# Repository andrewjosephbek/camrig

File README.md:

# Motorized Camera Tracking Rig

This project implements a compact Camera Motion Platform; integrating custom electronics, embedded firmware, and low-backlash mechanical design. Version 2 is currently in progress (UI firmware is finished, PCB Layout is finished, housing IP)! V1 KiCAD files are for an old version, may be incomplete. 

---

## Version 1: Demo
[Overview Video](https://youtu.be/gTk2HjM0wyA) (1:53)

---

## Version 2: PCB

### 3D:

### Layer 1 (Signal):

### Layer 2 (Ground):

### Layer 3 (Power):

### Layer 4 (Signal):

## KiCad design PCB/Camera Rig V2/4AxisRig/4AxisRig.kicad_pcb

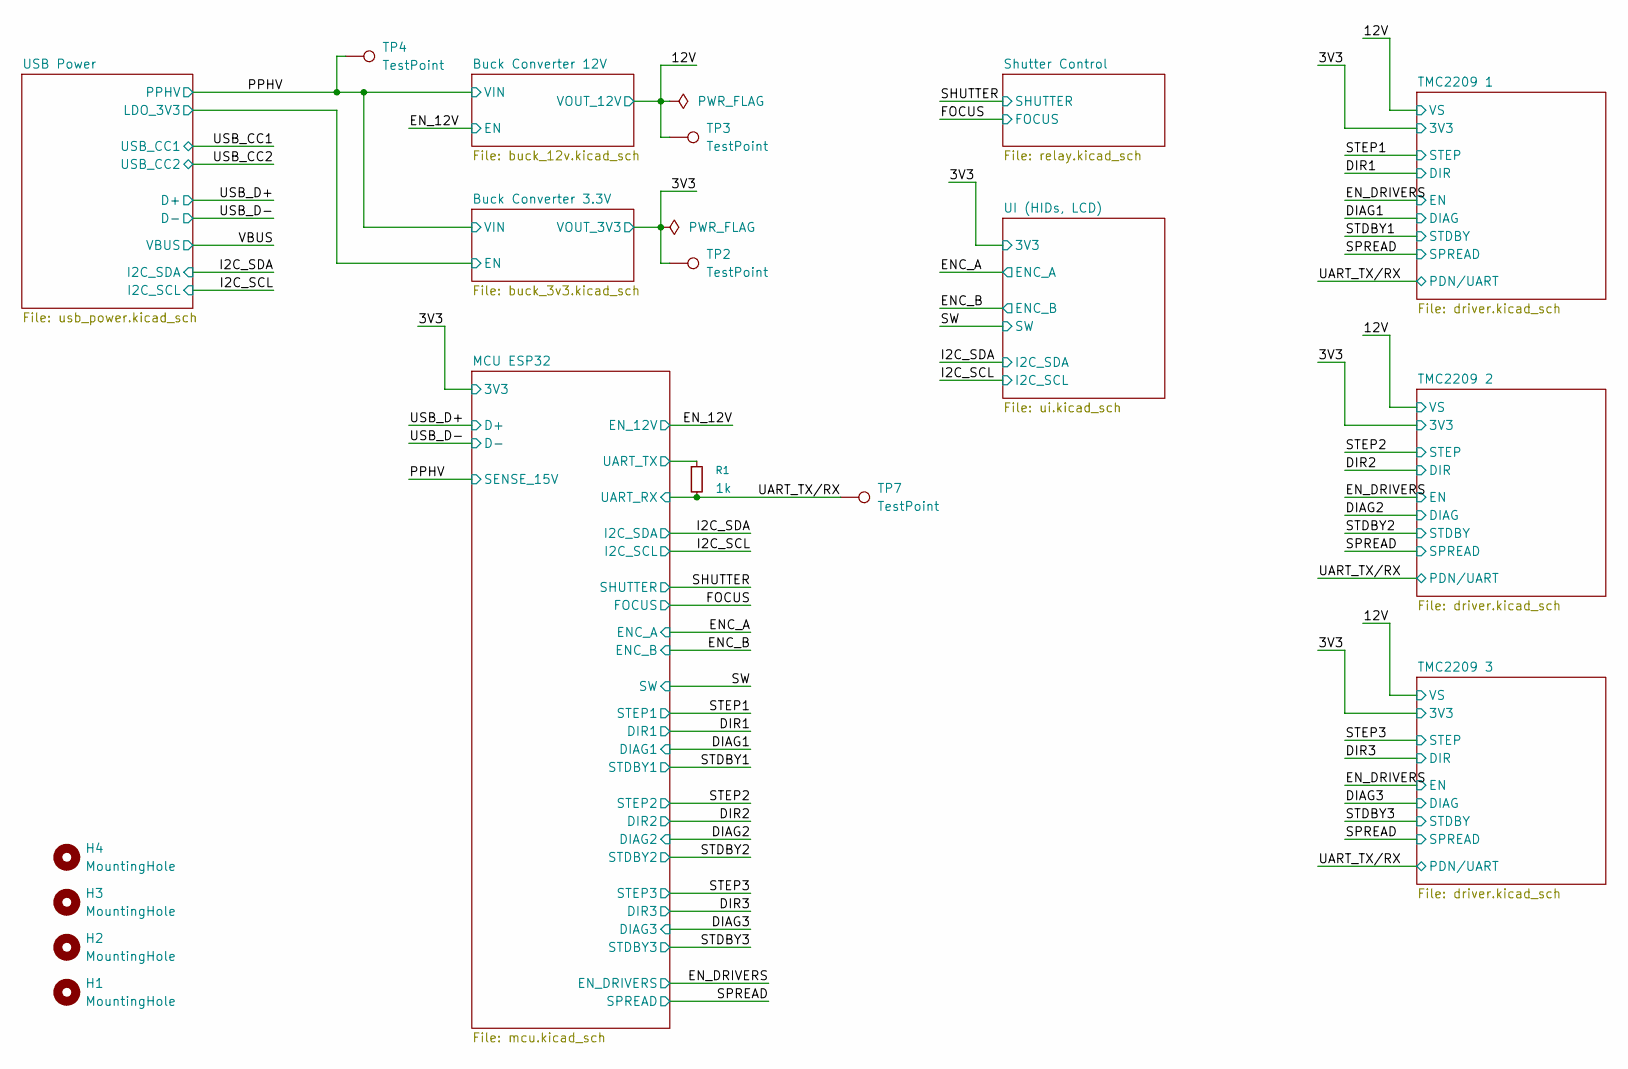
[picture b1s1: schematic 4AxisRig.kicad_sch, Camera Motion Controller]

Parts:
H1, H2, H3, H4: MountingHole; MountingHole_3.2mm_M3
R1: 1k; R_0603_1608Metric_Pad0.98x0.95mm_HandSolder
TP2, TP3, TP4: TestPoint; TestPoint_Pad_1.0x1.0mm
TP7: TestPoint; TestPoint_Keystone_5000-5004_Miniature

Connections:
/3V3: TP2.1; also elsewhere on the board
/12V: TP3.1; also elsewhere on the board
/MCU ESP32/UART_TX: R1.1; also elsewhere on the board
/PPHV: TP4.1; also elsewhere on the board
/UART_TX/RX: R1.2, TP7.1; also elsewhere on the board

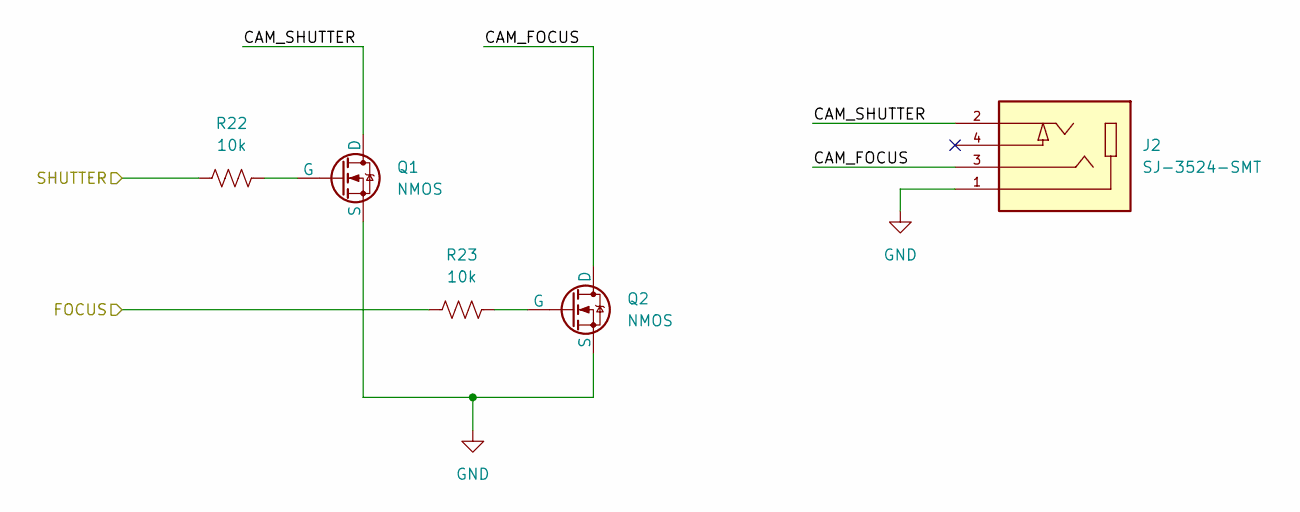
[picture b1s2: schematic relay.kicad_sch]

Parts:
J2: SJ-3524-SMT; CUI_SJ-3524-SMT; PARTREV 1.03; DigiKey_Part_Number CP-3524SJCT-ND
Q1, Q2: NMOS; SOT95P240X111-3N; Part Number 2N7002K
R22, R23: 10k; R_0603_1608Metric_Pad0.98x0.95mm_HandSolder

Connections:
/FOCUS: R23.1; also elsewhere on the board
/SHUTTER: R22.1; also elsewhere on the board
/Shutter Control/CAM_FOCUS: J2.3, Q2.1 (D)
/Shutter Control/CAM_SHUTTER: J2.2, Q1.1 (D)
GND: J2.1, Q1.3 (S), Q2.3 (S); also elsewhere on the board
unnamed: Q1.2 (G), R22.2
unnamed: Q2.2 (G), R23.2

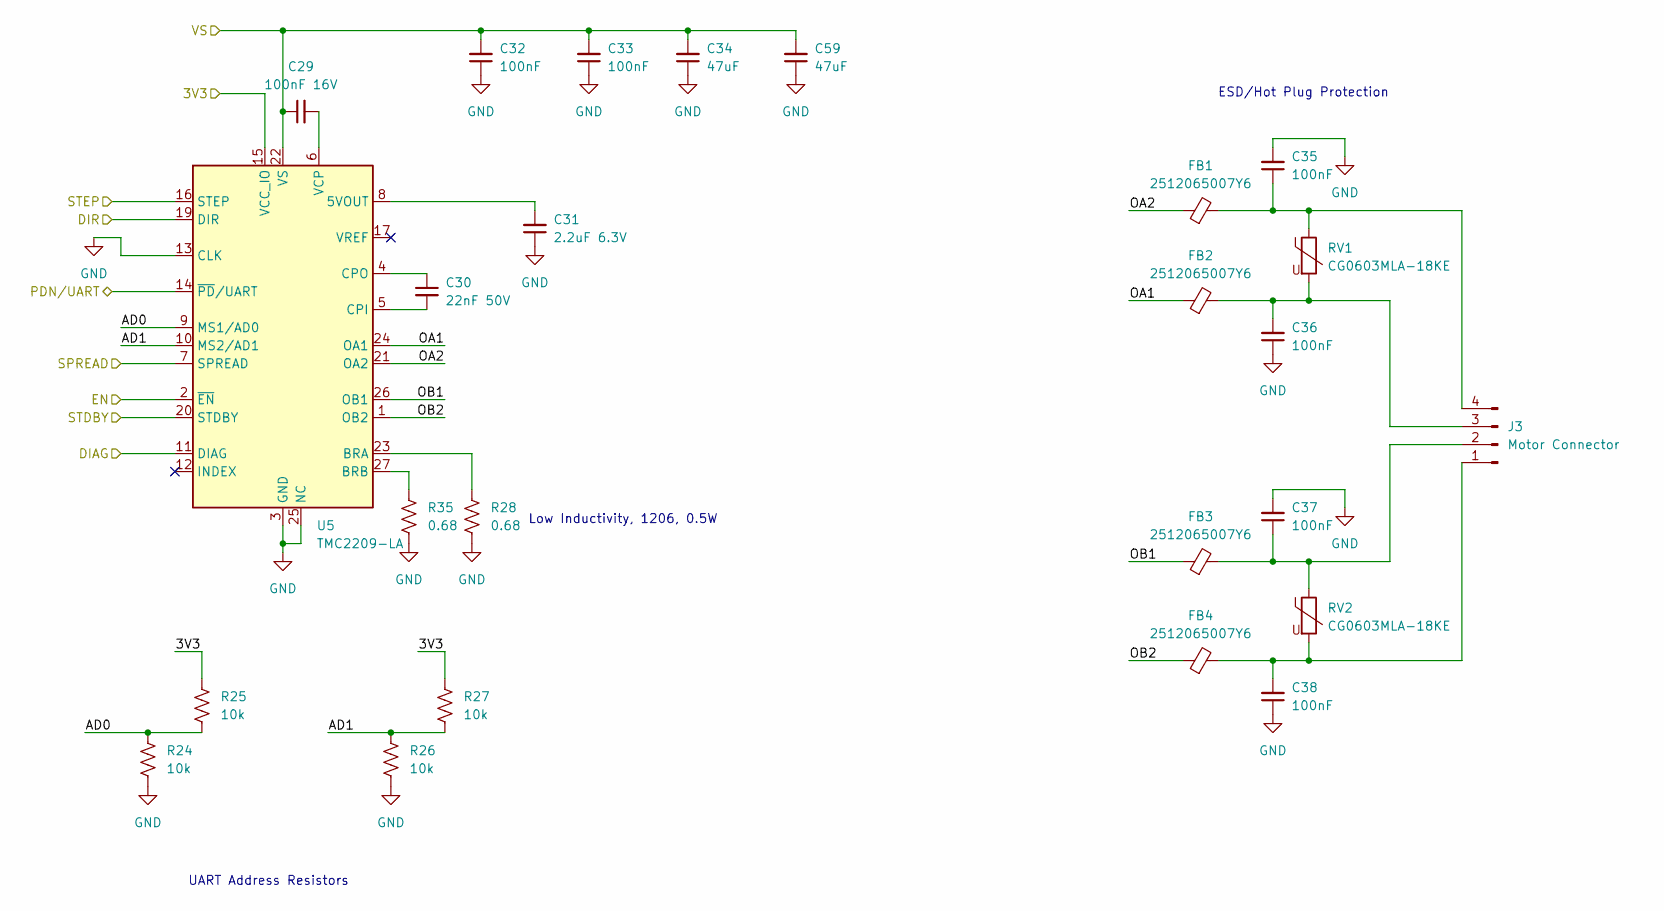
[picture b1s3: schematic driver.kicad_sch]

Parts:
C29: 100nF 16V; C_0603_1608Metric_Pad1.08x0.95mm_HandSolder
C30: 22nF 50V; C_0603_1608Metric_Pad1.08x0.95mm_HandSolder
C31: 2.2uF 6.3V; C_0603_1608Metric_Pad1.08x0.95mm_HandSolder
C32, C33, C35, C36, C37, C38: 100nF; C_0603_1608Metric_Pad1.08x0.95mm_HandSolder
C34, C59: 47uF; C_1210_3225Metric_Pad1.33x2.70mm_HandSolder
FB1, FB2, FB3, FB4: 2512065007Y6; L_1206_3216Metric_Pad1.22x1.90mm_HandSolder
J3: Motor Connector; PinHeader_1x04_P2.54mm_Horizontal
R24, R25, R26, R27: 10k; R_0603_1608Metric_Pad0.98x0.95mm_HandSolder
R28, R35: 0.68; R_1206_3216Metric_Pad1.30x1.75mm_HandSolder
RV1, RV2: CG0603MLA-18KE; R_1206_3216Metric_Pad1.30x1.75mm_HandSolder
U5: TMC2209-LA; VQFN-28-1EP_5x5mm_P0.5mm_EP3.7x3.7mm_ThermalVias; Part Number TMC2209-LA

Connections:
/3V3: R25.2, R27.2, U5.15 (VCC_IO); also elsewhere on the board
/12V: C29.1, C32.2, C33.2, C34.2, C59.2, U5.22 (VS), U5.28 (VS); also elsewhere on the board
/DIAG1: U5.11 (DIAG); also elsewhere on the board
/DIR1: U5.19 (DIR); also elsewhere on the board
/EN_DRIVERS: U5.2 (~EN); also elsewhere on the board
/SPREAD: U5.7 (SPREAD); also elsewhere on the board
/STDBY1: U5.20 (STDBY); also elsewhere on the board
/STEP1: U5.16 (STEP); also elsewhere on the board
/TMC2209 1/AD0: R24.2, R25.1, U5.9 (MS1/AD0)
/TMC2209 1/AD1: R26.2, R27.1, U5.10 (MS2/AD1)
/TMC2209 1/OA1: FB2.1, U5.24 (OA1)
/TMC2209 1/OA2: FB1.1, U5.21 (OA2)
/TMC2209 1/OB1: FB3.1, U5.26 (OB1)
/TMC2209 1/OB2: FB4.1, U5.1 (OB2)
/UART_TX/RX: U5.14 (~PD/UART); also elsewhere on the board
GND: C31.1, C32.1, C33.1, C34.1, C35.2, C36.1, C37.2, C38.1, C59.1, R24.1, R26.1, R28.1, R35.1, U5.3 (GND), U5.13 (CLK), U5.18 (GND), U5.25 (NC), U5.29 (GND); also elsewhere on the board
unnamed: C38.2, FB4.2, J3.1, RV2.2
unnamed: C37.1, FB3.2, J3.2, RV2.1
unnamed: C36.2, FB2.2, J3.3, RV1.2
unnamed: C35.1, FB1.2, J3.4, RV1.1
unnamed: C31.2, U5.8 (5VOUT)
unnamed: R28.2, U5.23 (BRA)
unnamed: R35.2, U5.27 (BRB)
unnamed: C30.2, U5.5 (CPI)
unnamed: C30.1, U5.4 (CPO)
unnamed: C29.2, U5.6 (VCP)

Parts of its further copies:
C39, C49: 100nF 16V; C_0603_1608Metric_Pad1.08x0.95mm_HandSolder
C40, C50: 22nF 50V; C_0603_1608Metric_Pad1.08x0.95mm_HandSolder
C41, C51: 2.2uF 6.3V; C_0603_1608Metric_Pad1.08x0.95mm_HandSolder
C42, C43, C45, C46, C47, C48, C52, C53, C55, C56, C57, C58: 100nF; C_0603_1608Metric_Pad1.08x0.95mm_HandSolder
C44, C54, C60, C61: 47uF; C_1210_3225Metric_Pad1.33x2.70mm_HandSolder
FB5, FB6, FB7, FB8, FB9, FB10, FB11, FB12: 2512065007Y6; L_1206_3216Metric_Pad1.22x1.90mm_HandSolder
J4, J6: Motor Connector; PinHeader_1x04_P2.54mm_Horizontal
R29, R34, R42, R43: 0.68; R_1206_3216Metric_Pad1.30x1.75mm_HandSolder
R30, R31, R32, R33, R38, R39, R40, R41: 10k; R_0603_1608Metric_Pad0.98x0.95mm_HandSolder
RV3, RV4, RV5, RV6: CG0603MLA-18KE; R_1206_3216Metric_Pad1.30x1.75mm_HandSolder
U6, U7: TMC2209-LA; VQFN-28-1EP_5x5mm_P0.5mm_EP3.7x3.7mm_ThermalVias; Part Number TMC2209-LA

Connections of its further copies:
/3V3: R31.2, R33.2, R39.2, R41.2, U6.15 (VCC_IO), U7.15 (VCC_IO); also elsewhere on the board
/12V: C39.1, C42.2, C43.2, C44.2, C49.1, C52.2, C53.2, C54.2, C60.2, C61.2, U6.22 (VS), U6.28 (VS), U7.22 (VS), U7.28 (VS); also elsewhere on the board
/DIAG2: U6.11 (DIAG); also elsewhere on the board
/DIAG3: U7.11 (DIAG); also elsewhere on the board
/DIR2: U6.19 (DIR); also elsewhere on the board
/DIR3: U7.19 (DIR); also elsewhere on the board
/EN_DRIVERS: U6.2 (~EN), U7.2 (~EN); also elsewhere on the board
/SPREAD: U6.7 (SPREAD), U7.7 (SPREAD); also elsewhere on the board
/STDBY2: U6.20 (STDBY); also elsewhere on the board
/STDBY3: U7.20 (STDBY); also elsewhere on the board
/STEP2: U6.16 (STEP); also elsewhere on the board
/STEP3: U7.16 (STEP); also elsewhere on the board
/TMC2209 2/AD0: R30.2, R31.1, U6.9 (MS1/AD0)
/TMC2209 2/AD1: R32.2, R33.1, U6.10 (MS2/AD1)
/TMC2209 2/OA1: FB6.1, U6.24 (OA1)
/TMC2209 2/OA2: FB5.1, U6.21 (OA2)
/TMC2209 2/OB1: FB7.1, U6.26 (OB1)
/TMC2209 2/OB2: FB8.1, U6.1 (OB2)
/TMC2209 3/AD0: R38.2, R39.1, U7.9 (MS1/AD0)
/TMC2209 3/AD1: R40.2, R41.1, U7.10 (MS2/AD1)
/TMC2209 3/OA1: FB10.1, U7.24 (OA1)
/TMC2209 3/OA2: FB9.1, U7.21 (OA2)
/TMC2209 3/OB1: FB11.1, U7.26 (OB1)
/TMC2209 3/OB2: FB12.1, U7.1 (OB2)
/UART_TX/RX: U6.14 (~PD/UART), U7.14 (~PD/UART); also elsewhere on the board
GND: C41.1, C42.1, C43.1, C44.1, C45.2, C46.1, C47.2, C48.1, C51.1, C52.1, C53.1, C54.1, C55.2, C56.1, C57.2, C58.1, C60.1, C61.1, R29.1, R30.1, R32.1, R34.1, R38.1, R40.1, R42.1, R43.1, U6.3 (GND), U6.13 (CLK), U6.18 (GND), U6.25 (NC), U6.29 (GND), U7.3 (GND), U7.13 (CLK), U7.18 (GND), U7.25 (NC), U7.29 (GND); also elsewhere on the board
unnamed: C48.2, FB8.2, J4.1, RV4.2
unnamed: C47.1, FB7.2, J4.2, RV4.1
unnamed: C46.2, FB6.2, J4.3, RV3.2
unnamed: C45.1, FB5.2, J4.4, RV3.1
unnamed: C58.2, FB12.2, J6.1, RV6.2
unnamed: C57.1, FB11.2, J6.2, RV6.1
unnamed: C56.2, FB10.2, J6.3, RV5.2
unnamed: C55.1, FB9.2, J6.4, RV5.1
unnamed: C41.2, U6.8 (5VOUT)
unnamed: R29.2, U6.23 (BRA)
unnamed: R42.2, U6.27 (BRB)
unnamed: C40.2, U6.5 (CPI)
unnamed: C40.1, U6.4 (CPO)
unnamed: C39.2, U6.6 (VCP)
unnamed: C51.2, U7.8 (5VOUT)
unnamed: R34.2, U7.23 (BRA)
unnamed: R43.2, U7.27 (BRB)
unnamed: C50.2, U7.5 (CPI)
unnamed: C50.1, U7.4 (CPO)
unnamed: C49.2, U7.6 (VCP)

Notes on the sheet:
UART Address Resistors
ESD/Hot Plug Protection
Low Inductivity, 1206, 0.5W

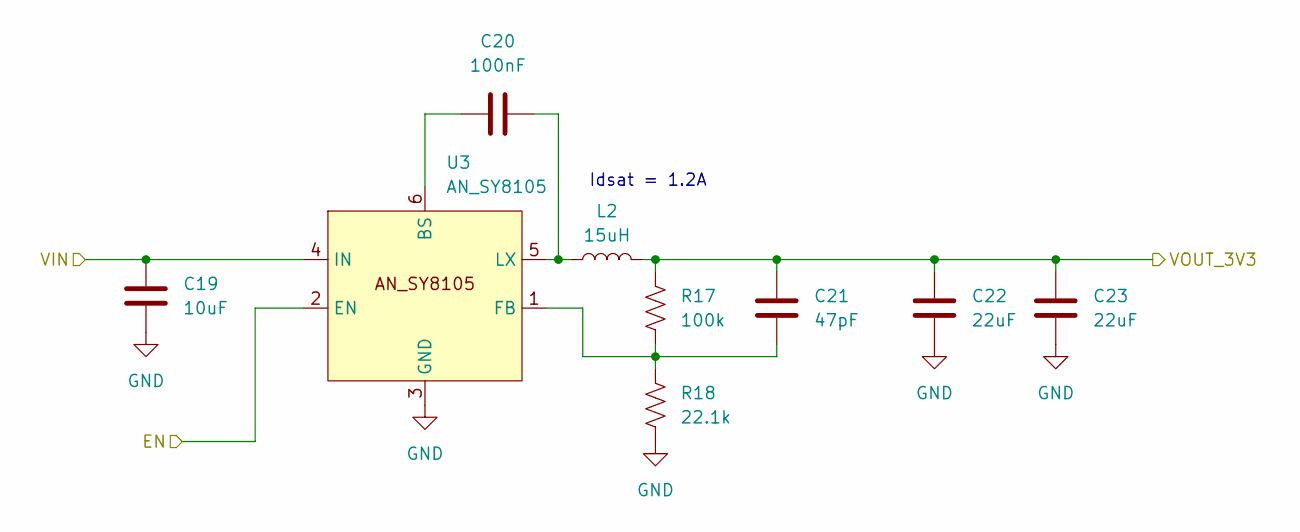
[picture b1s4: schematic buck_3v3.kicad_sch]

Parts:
C19: 10uF; C_0603_1608Metric_Pad1.08x0.95mm_HandSolder
C20: 100nF; C_0603_1608Metric_Pad1.08x0.95mm_HandSolder
C21: 47pF; C_0603_1608Metric_Pad1.08x0.95mm_HandSolder
C22, C23: 22uF; C_1206_3216Metric_Pad1.33x1.80mm_HandSolder
L2: 15uH; DR74; Part Number DR74-150-R
R17: 100k; R_0603_1608Metric_Pad0.98x0.95mm_HandSolder
R18: 22.1k; R_0603_1608Metric_Pad0.98x0.95mm_HandSolder
U3: AN_SY8105; TSOT-23-6_HandSoldering; Part Number AN_SY8105

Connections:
/3V3: C21.1, C22.1, C23.1, L2.2, R17.1; also elsewhere on the board
/PPHV: C19.1, U3.4 (IN); also elsewhere on the board
/USB Power/LDO_3V3: U3.2 (EN); also elsewhere on the board
GND: C19.2, C22.2, C23.2, R18.2, U3.3 (GND); also elsewhere on the board
unnamed: C20.2, U3.6 (BS)
unnamed: C21.2, R17.2, R18.1, U3.1 (FB)
unnamed: C20.1, L2.1, U3.5 (LX)

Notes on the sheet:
Idsat = 1.2A

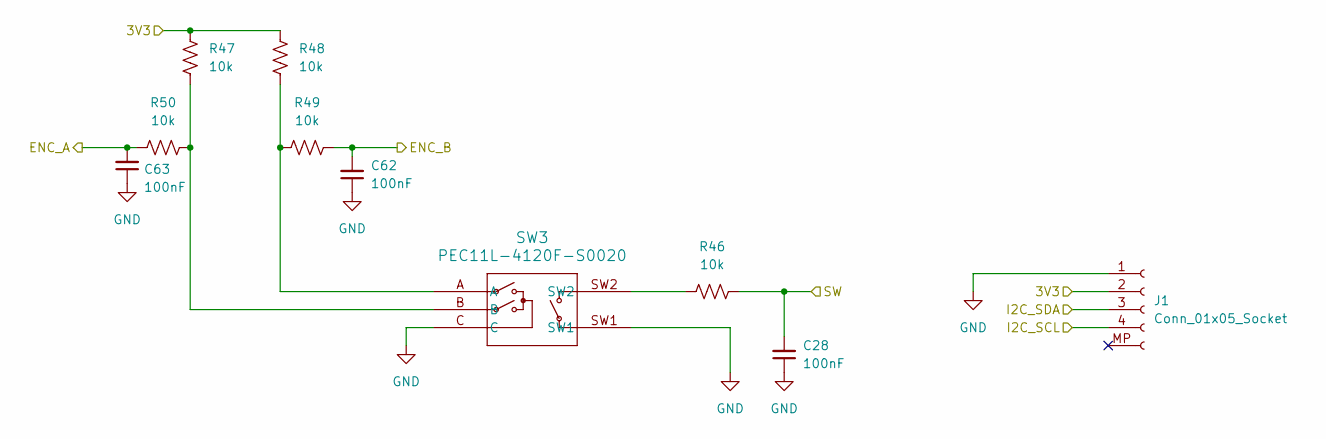
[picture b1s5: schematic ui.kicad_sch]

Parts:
C28, C62, C63: 100nF; C_0603_1608Metric_Pad1.08x0.95mm_HandSolder
J1: Conn_01x05_Socket; JST_SH_BM04B-SRSS-TB_1x04-1MP_P1.00mm_Vertical
R46, R47, R48, R49, R50: 10k; R_0603_1608Metric_Pad0.98x0.95mm_HandSolder
SW3: PEC11L-4120F-S0020; PEC11L-4x20F-Sxxx_BRN

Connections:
/3V3: J1.2, R47.1, R48.1; also elsewhere on the board
/ENC_A: C63.2, R50.1; also elsewhere on the board
/ENC_B: C62.2, R49.2; also elsewhere on the board
/I2C_SCL: J1.4; also elsewhere on the board
/I2C_SDA: J1.3; also elsewhere on the board
/SW: C28.2, R46.1; also elsewhere on the board
GND: C28.1, C62.1, C63.1, J1.1, SW3.C, SW3.SW1; also elsewhere on the board
unnamed: R46.2, SW3.SW2
unnamed: R47.2, R50.2, SW3.B
unnamed: R48.2, R49.1, SW3.A

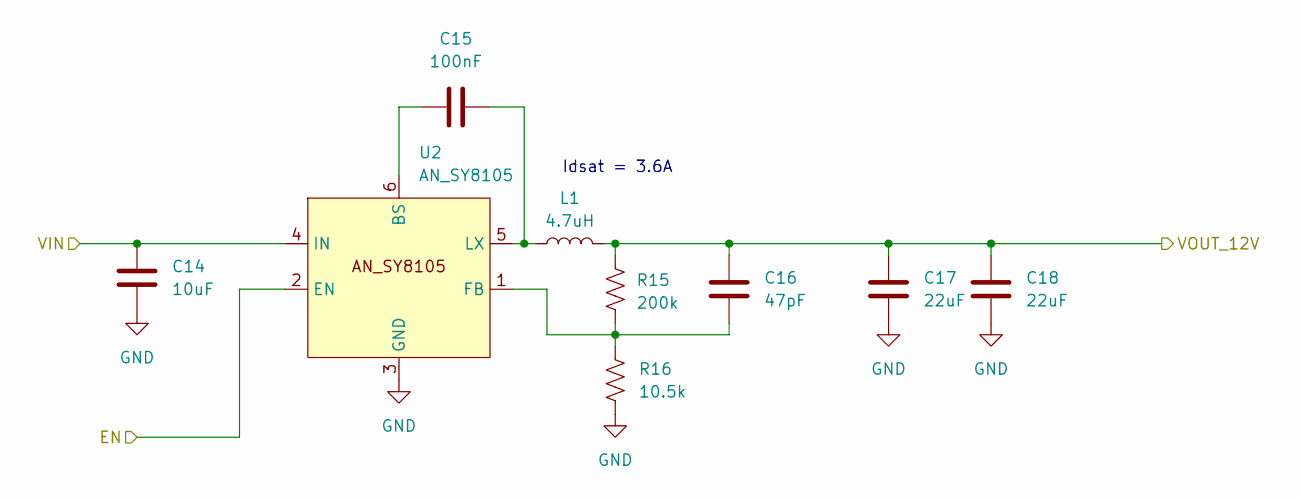
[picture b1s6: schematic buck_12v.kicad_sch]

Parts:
C14: 10uF; C_0603_1608Metric_Pad1.08x0.95mm_HandSolder
C15: 100nF; C_0603_1608Metric_Pad1.08x0.95mm_HandSolder
C16: 47pF; C_0603_1608Metric_Pad1.08x0.95mm_HandSolder
C17, C18: 22uF; C_1206_3216Metric_Pad1.33x1.80mm_HandSolder
L1: 4.7uH; DR74; Part Number DR74-4R7-R
R15: 200k; R_0603_1608Metric_Pad0.98x0.95mm_HandSolder
R16: 10.5k; R_0603_1608Metric_Pad0.98x0.95mm_HandSolder
U2: AN_SY8105; TSOT-23-6_HandSoldering; Part Number AN_SY8105

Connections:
/12V: C16.1, C17.1, C18.1, L1.2, R15.1; also elsewhere on the board
/EN_12V: U2.2 (EN); also elsewhere on the board
/PPHV: C14.1, U2.4 (IN); also elsewhere on the board
GND: C14.2, C17.2, C18.2, R16.2, U2.3 (GND); also elsewhere on the board
unnamed: C15.2, U2.6 (BS)
unnamed: C16.2, R15.2, R16.1, U2.1 (FB)
unnamed: C15.1, L1.1, U2.5 (LX)

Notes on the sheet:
Idsat = 3.6A

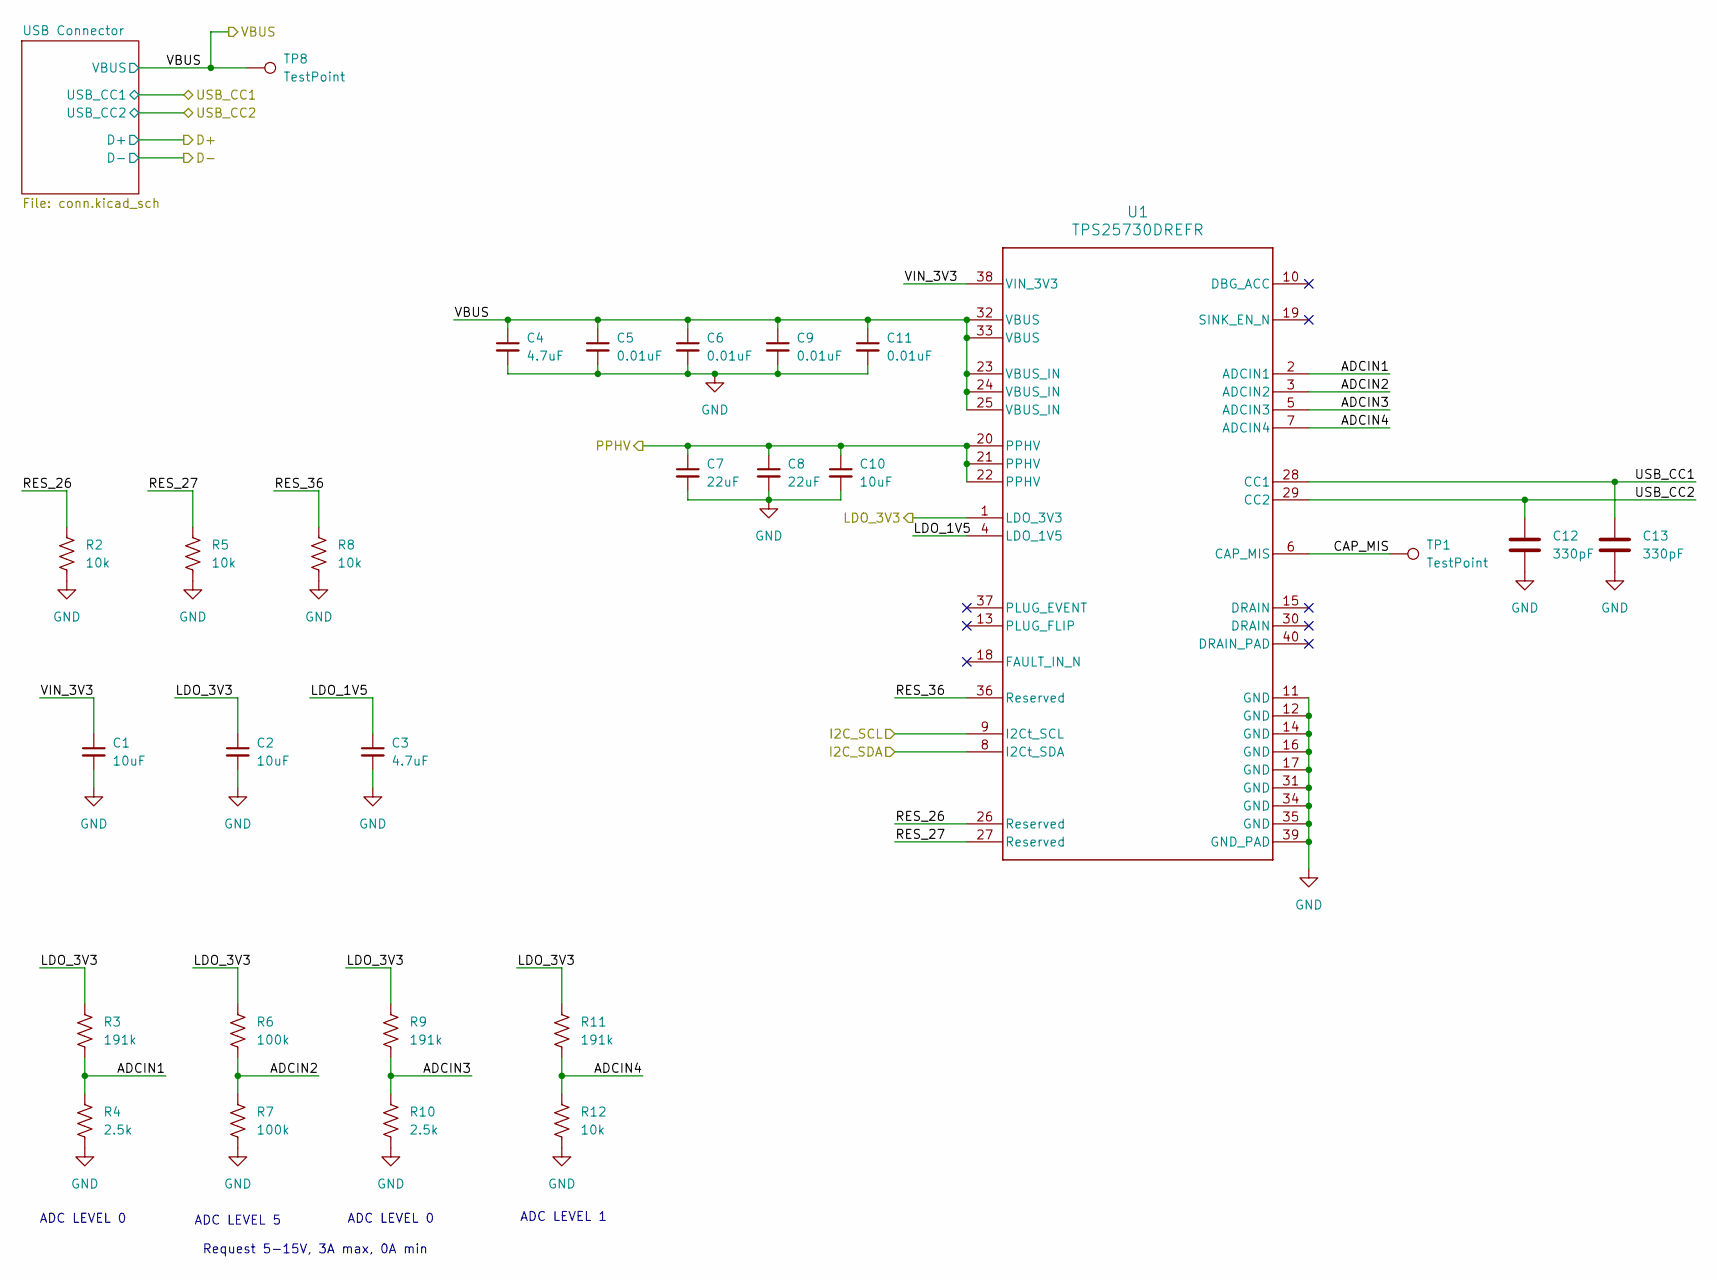
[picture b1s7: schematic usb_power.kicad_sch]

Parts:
C1, C2, C10: 10uF; C_0603_1608Metric_Pad1.08x0.95mm_HandSolder
C3, C4: 4.7uF; C_0603_1608Metric_Pad1.08x0.95mm_HandSolder
C5, C6, C9, C11: 0.01uF; C_0603_1608Metric_Pad1.08x0.95mm_HandSolder
C7, C8: 22uF; C_1206_3216Metric_Pad1.33x1.80mm_HandSolder
C12, C13: 330pF; C_0603_1608Metric_Pad1.08x0.95mm_HandSolder
R2, R5, R8, R12: 10k; R_0603_1608Metric_Pad0.98x0.95mm_HandSolder
R3, R9, R11: 191k; R_0603_1608Metric_Pad0.98x0.95mm_HandSolder
R4, R10: 2.5k; R_0603_1608Metric_Pad0.98x0.95mm_HandSolder
R6, R7: 100k; R_0603_1608Metric_Pad0.98x0.95mm_HandSolder
TP1, TP8: TestPoint; TestPoint_Pad_1.0x1.0mm
U1: TPS25730DREFR; REF0038A-MFG; Part Number TPS25730DREFR

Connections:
/I2C_SCL: U1.9 (I2Ct_SCL); also elsewhere on the board
/I2C_SDA: U1.8 (I2Ct_SDA); also elsewhere on the board
/PPHV: C7.1, C8.1, C10.1, U1.20 (PPHV), U1.21 (PPHV), U1.22 (PPHV); also elsewhere on the board
/USB Power/ADCIN1: R3.2, R4.1, U1.2 (ADCIN1)
/USB Power/ADCIN2: R6.2, R7.1, U1.3 (ADCIN2)
/USB Power/ADCIN3: R9.2, R10.1, U1.5 (ADCIN3)
/USB Power/ADCIN4: R11.2, R12.1, U1.7 (ADCIN4)
/USB Power/CAP_MIS: TP1.1, U1.6 (CAP_MIS)
/USB Power/LDO_1V5: C3.1, U1.4 (LDO_1V5)
/USB Power/LDO_3V3: C2.1, R3.1, R6.1, R9.1, R11.1, U1.1 (LDO_3V3); also elsewhere on the board
/USB Power/RES_26: R2.1, U1.26 (Reserved)
/USB Power/RES_27: R5.1, U1.27 (Reserved)
/USB Power/RES_36: R8.1, U1.36 (Reserved)
/USB Power/VIN_3V3: C1.1, U1.38 (VIN_3V3)
/USB_CC1: C13.1, U1.28 (CC1); also elsewhere on the board
/USB_CC2: C12.1, U1.29 (CC2); also elsewhere on the board
/VBUS: C4.1, C5.1, C6.1, C9.1, C11.1, TP8.1, U1.23 (VBUS_IN), U1.24 (VBUS_IN), U1.25 (VBUS_IN), U1.32 (VBUS), U1.33 (VBUS); also elsewhere on the board
GND: C1.2, C2.2, C3.2, C4.2, C5.2, C6.2, C7.2, C8.2, C9.2, C10.2, C11.2, C12.2, C13.2, R2.2, R4.2, R5.2, R7.2, R8.2, R10.2, R12.2, U1.11 (GND), U1.12 (GND), U1.14 (GND), U1.16 (GND), U1.17 (GND), U1.31 (GND), U1.34 (GND), U1.35 (GND), U1.39 (GND_PAD); also elsewhere on the board

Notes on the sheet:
Request 5-15V, 3A max, 0A min
ADC LEVEL 5
ADC LEVEL 0
ADC LEVEL 0
ADC LEVEL 1

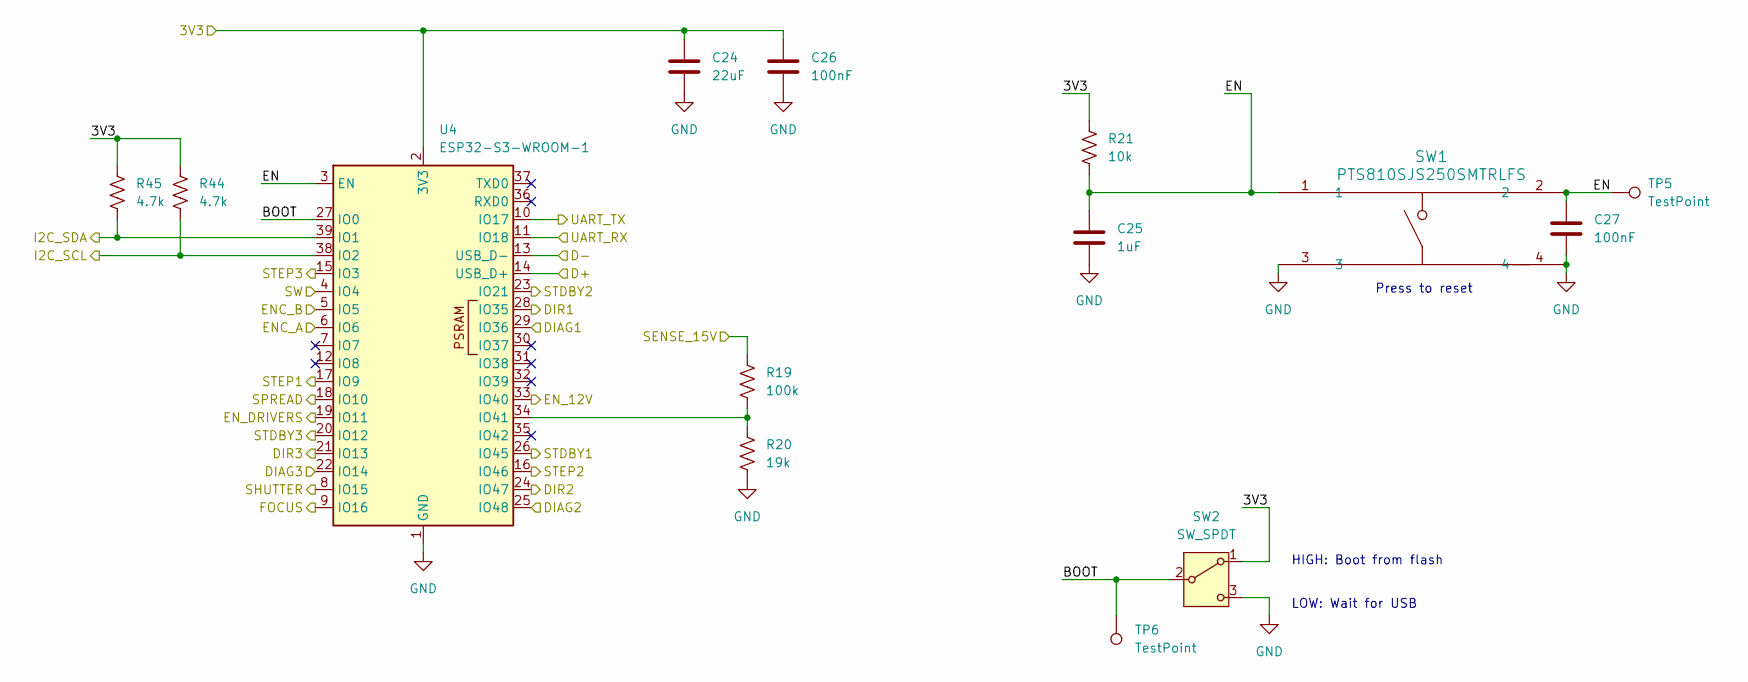
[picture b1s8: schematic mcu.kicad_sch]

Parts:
C24: 22uF; C_1206_3216Metric_Pad1.33x1.80mm_HandSolder
C25: 1uF; C_0603_1608Metric_Pad1.08x0.95mm_HandSolder
C26, C27: 100nF; C_0603_1608Metric_Pad1.08x0.95mm_HandSolder
R19: 100k; R_0603_1608Metric_Pad0.98x0.95mm_HandSolder
R20: 19k; R_0603_1608Metric_Pad0.98x0.95mm_HandSolder
R21: 10k; R_0603_1608Metric_Pad0.98x0.95mm_HandSolder
R44, R45: 4.7k; R_0603_1608Metric_Pad0.98x0.95mm_HandSolder
SW1: PTS810SJS250SMTRLFS; SMT_MTRLFS_CNK
SW2: SW_SPDT; SS12D07_CNK
TP5, TP6: TestPoint; TestPoint_Pad_1.0x1.0mm
U4: ESP32-S3-WROOM-1; Part Number ESP32-S3-WROOM-1

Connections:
/3V3: C24.1, C26.1, R21.2, R44.2, R45.2, SW2.1 (A), U4.2 (3V3); also elsewhere on the board
/DIAG1: U4.29 (IO36); also elsewhere on the board
/DIAG2: U4.25 (IO48); also elsewhere on the board
/DIAG3: U4.22 (IO14); also elsewhere on the board
/DIR1: U4.28 (IO35); also elsewhere on the board
/DIR2: U4.24 (IO47); also elsewhere on the board
/DIR3: U4.21 (IO13); also elsewhere on the board
/ENC_A: U4.6 (IO6); also elsewhere on the board
/ENC_B: U4.5 (IO5); also elsewhere on the board
/EN_12V: U4.33 (IO40); also elsewhere on the board
/EN_DRIVERS: U4.19 (IO11); also elsewhere on the board
/FOCUS: U4.9 (IO16); also elsewhere on the board
/I2C_SCL: R44.1, U4.38 (IO2); also elsewhere on the board
/I2C_SDA: R45.1, U4.39 (IO1); also elsewhere on the board
/MCU ESP32/BOOT: SW2.2 (B), TP6.1, U4.27 (IO0)
/MCU ESP32/EN: C25.2, C27.1, R21.1, SW1.1, SW1.2, TP5.1, U4.3 (EN)
/MCU ESP32/UART_TX: U4.10 (IO17); also elsewhere on the board
/PPHV: R19.2; also elsewhere on the board
/SHUTTER: U4.8 (IO15); also elsewhere on the board
/SPREAD: U4.18 (IO10); also elsewhere on the board
/STDBY1: U4.26 (IO45); also elsewhere on the board
/STDBY2: U4.23 (IO21); also elsewhere on the board
/STDBY3: U4.20 (IO12); also elsewhere on the board
/STEP1: U4.17 (IO9); also elsewhere on the board
/STEP2: U4.16 (IO46); also elsewhere on the board
/STEP3: U4.15 (IO3); also elsewhere on the board
/SW: U4.4 (IO4); also elsewhere on the board
/UART_TX/RX: U4.11 (IO18); also elsewhere on the board
/USB_D+: U4.14 (USB_D+); also elsewhere on the board
/USB_D-: U4.13 (USB_D-); also elsewhere on the board
GND: C24.2, C25.1, C26.2, C27.2, R20.1, SW1.3, SW1.4, SW2.3 (C), U4.1 (GND), U4.40 (GND), U4.41 (GND); also elsewhere on the board
unnamed: R19.1, R20.2, U4.34 (IO41)

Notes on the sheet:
Press to reset
HIGH: Boot from flash LOW: Wait for USB

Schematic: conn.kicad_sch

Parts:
D1, D2, D3, D4: ESD441; D_0402_1005Metric_Pad0.77x0.64mm_HandSolder
D5: T4F10A; Nexperia_CFP3_SOD-123W
J5: USB_C_Receptacle_USB2.0_16P; CONN_8p94X6p5X3p16_12L_GCC
R36, R37: 5.1k+-10%; R_0603_1608Metric_Pad0.98x0.95mm_HandSolder

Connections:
/USB_CC1: D3.1 (K), J5.A5 (CC1), R36.1; also elsewhere on the board
/USB_CC2: D4.1 (K), J5.B5 (CC2), R37.1; also elsewhere on the board
/USB_D+: D1.1 (K), J5.A6 (D+), J5.B6 (D+); also elsewhere on the board
/USB_D-: D2.1 (K), J5.A7 (D-), J5.B7 (D-); also elsewhere on the board
/VBUS: D5.1 (K), J5.A4 (VBUS), J5.A9 (VBUS), J5.B4 (VBUS), J5.B9 (VBUS); also elsewhere on the board
GND: D1.2 (A), D2.2 (A), D3.2 (A), D4.2 (A), D5.2 (A), J5.A1 (GND), J5.A12 (GND), J5.B1 (GND), J5.B12 (GND), J5.S1 (SHIELD), R36.2, R37.2; also elsewhere on the board

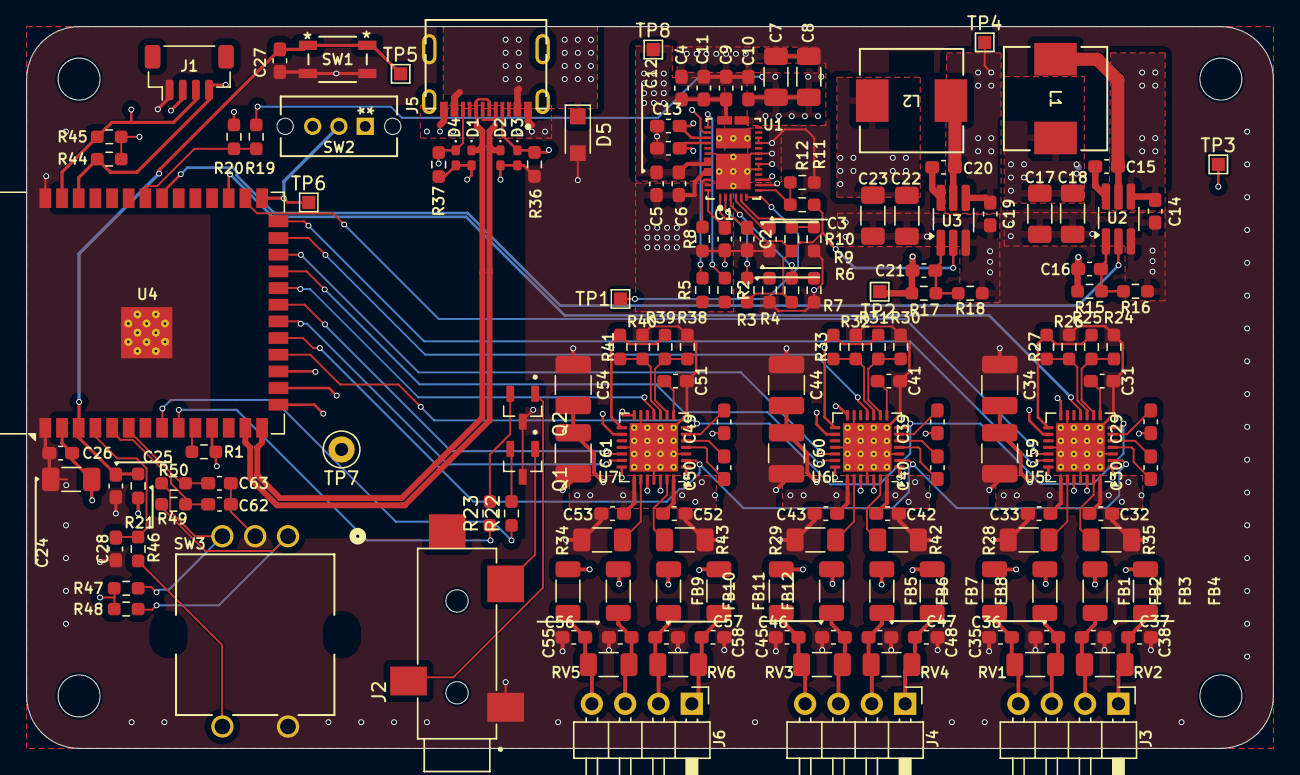
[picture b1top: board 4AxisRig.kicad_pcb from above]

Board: 4 copper layers, 95.0 x 55.0 mm, 166 parts (0 on the bottom side), 108 nets.

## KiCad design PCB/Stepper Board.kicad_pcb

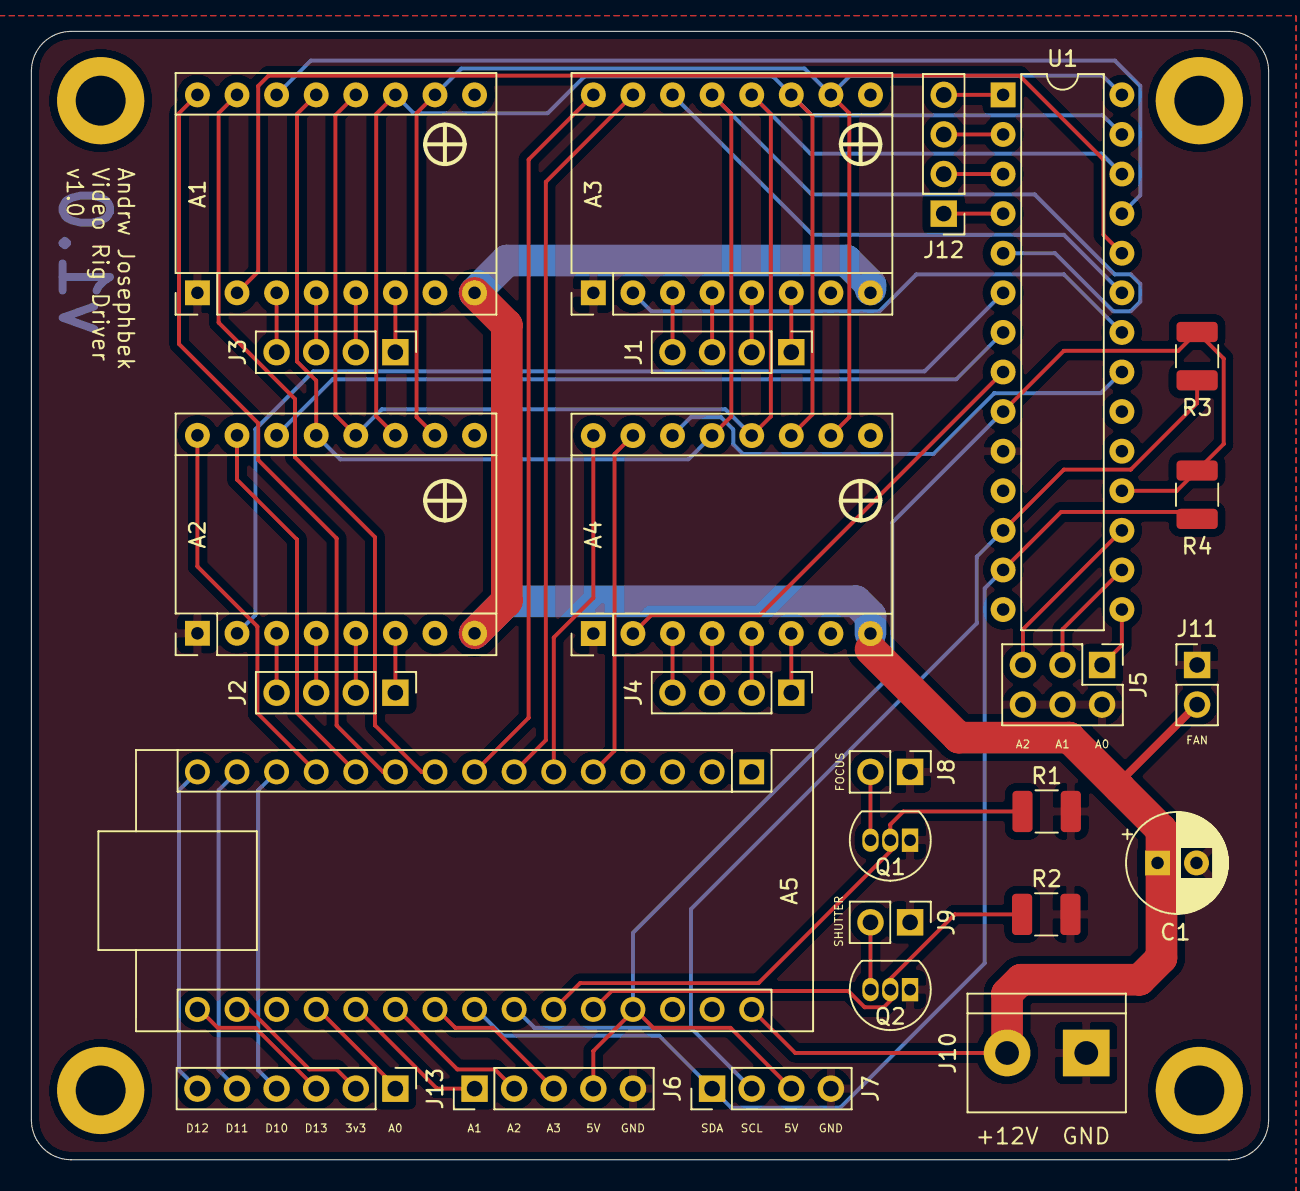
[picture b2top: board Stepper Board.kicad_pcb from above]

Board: 2 copper layers, 79.4 x 72.4 mm, 30 parts (0 on the bottom side), 61 nets.

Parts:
 : MountingHole_3.2mm_M3_DIN965_Pad
 #2,  #3,  #4: MountingHole_3.2mm_M3_DIN965_Pad
A1, A2, A3, A4: Pololu_Breakout_DRV8825; Pololu_Breakout-16_15.2x20.3mm
A5: Arduino_Nano_v3.x; Arduino_Nano
C1: 220uF; CP_Radial_D6.3mm_P2.50mm
J1, J2, J3, J4: Stepper Header; PinHeader_1x04_P2.54mm_Vertical
J5: Address Header; PinHeader_2x03_P2.54mm_Vertical
J6: R.Encoder Header; PinHeader_1x05_P2.54mm_Vertical
J7: LCD Header; PinHeader_1x04_P2.54mm_Vertical
J8: Focus; PinHeader_1x02_P2.54mm_Vertical
J9: Shot; PinHeader_1x02_P2.54mm_Vertical
J10: Power (+12V); TerminalBlock_bornier-2_P5.08mm
J11: Fan Header; PinHeader_1x02_P2.54mm_Vertical
J12: Extra Header I2C; PinHeader_1x04_P2.54mm_Vertical
J13: Extra Header Direct; PinHeader_1x06_P2.54mm_Vertical
Q1, Q2: 2N7000; TO-92_Inline
R3, R4, R7, R8: SM 10K; R_1210_3225Metric_Pad1.30x2.65mm_HandSolder
U1: MCP23017_SP; DIP-28_W7.62mm

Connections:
+3V3: A5.17, J13.2
+5V: A5.27, J6.4, J7.3, R3.1, R4.1, U1.9, U1.18
A0: A5.19, J13.1
A1: A5.20, J6.1
A1(1): A1.4, J1.3
A1(2): A2.4, J2.3
A1(3): A3.4, J3.3
A1(4): A4.4, J4.3
A2: A5.21, J6.2
A2(1): A1.3, J1.4
A2(2): A2.3, J2.4
A2(3): A3.3, J3.4
A2(4): A4.3, J4.4
A3: A5.22, J6.3
A6: A5.25, Q1.2
A7: A5.26, Q2.2
B1(1): A1.5, J1.2
B1(2): A2.5, J2.2
B1(3): A3.5, J3.2
B1(4): A4.5, J4.2
B2(1): A1.6, J1.1
B2(2): A2.6, J2.1
B2(3): A3.6, J3.1
B2(4): A4.6, J4.1
D13: A5.16, J13.3
DIR1: A1.16, A5.8
DIR2: A2.16, A5.12
DIR3: A3.16, A5.10
DIR4: A4.16, A5.6
FLT1: A1.2, U1.22
FLT2: A2.2, U1.6
FLT3: A3.2, U1.24
FLT4: A4.2, U1.8
GND: A1.1, A2.1, A3.1, A4.1, A5.29, C1.2, J5.2, J5.4, J5.6, J6.5, J7.4, J8.1, J9.1, J10.1, J11.1, Q1.1, Q2.1, R7.1, R8.1, U1.10
M0: A1.10, A2.10, A3.10, A4.10, U1.28
M1: A1.11, A2.11, A3.11, A4.11, U1.27
M2: A1.12, A2.12, A3.12, A4.12, U1.26
unnamed: A5.13, J13.4
unnamed: A5.14, J13.5
unnamed: A5.15, J13.6
unnamed: J5.1, U1.15
unnamed: J5.3, U1.16
unnamed: J5.5, U1.17
unnamed: J8.2, Q1.3
unnamed: J9.2, Q2.3
unnamed: J12.1, U1.4
unnamed: J12.2, U1.3
unnamed: J12.3, U1.2
unnamed: J12.4, U1.1
RST: A1.13, A2.13, A3.13, A4.13, U1.5
SCK: A5.24, J7.2, R4.2, U1.12
SDA: A5.23, J7.1, R3.2, U1.13
SLEEP1: A1.14, U1.23
SLEEP2: A2.14, U1.7
SLEEP3: A3.14, U1.25
SLEEP4: A4.14, U1.21
STEP1: A1.15, A5.7
STEP2: A2.15, A5.11
STEP3: A3.15, A5.9
STEP4: A4.15, A5.5
VCC: A1.8, A2.8, A3.8, A4.8, A5.30, C1.1, J10.2, J11.2

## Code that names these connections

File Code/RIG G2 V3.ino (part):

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#include <Adafruit_MCP23017.h>

//Definitions
#define STEP4 2
#define DIR4 3
#define STEP1 4
#define DIR1 5
#define STEP3 6
#define DIR3 7
#define STEP2 8
#define DIR2 9

#define SDA 4
#define SCL 5
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#define M2 5

#define RESET 12
#define SLEEP1 2
#define SLEEP2 14
#define SLEEP3 4
#define SLEEP4 0

#define FAULT1 1
#define FAULT2 13
#define FAULT3 3
#define FAULT4 15
#define FOCUS A6
#define SHOT A7

#define inputCLK A2
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void setup() {
  mcp.begin();
  //pinmodes
  pinMode(STEP4, OUTPUT);
  pinMode(DIR4, OUTPUT);
  pinMode(STEP1, OUTPUT);
  pinMode(DIR1, OUTPUT);
  pinMode(STEP3, OUTPUT);
  pinMode(DIR3, OUTPUT);
  pinMode(STEP2, OUTPUT);
  pinMode(DIR2, OUTPUT);
  pinMode(FOCUS, OUTPUT);
  pinMode(SHOT, OUTPUT);

  pinMode(inputCLK, INPUT);
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
  mcp.pinMode(RESET, OUTPUT);

  mcp.pinMode(SLEEP1, OUTPUT);
  mcp.pinMode(SLEEP2, OUTPUT);
  mcp.pinMode(SLEEP3, OUTPUT);
  mcp.pinMode(SLEEP4, OUTPUT);

  mcp.pinMode(FAULT1, INPUT);
  mcp.pinMode(FAULT2, INPUT);
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
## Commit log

2025-06-19 Initial Commit
    Moved files from local machine to GitHub
2025-06-19 Added 3D Files
2026-02-28 Brought in V2
2026-03-02 PCB V2 first draft
2026-03-03 REplaced bulk caps w low esr ceramics
2026-03-03 Updated rotary encoder wiring
2026-03-03 Updated figs
2026-03-10 Netclass Improvements
